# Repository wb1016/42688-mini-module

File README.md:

# 42688-mini-module
small module for ICM-42688-P compatible with BMI160 module form factor. supports I2C, I3C, SPI.

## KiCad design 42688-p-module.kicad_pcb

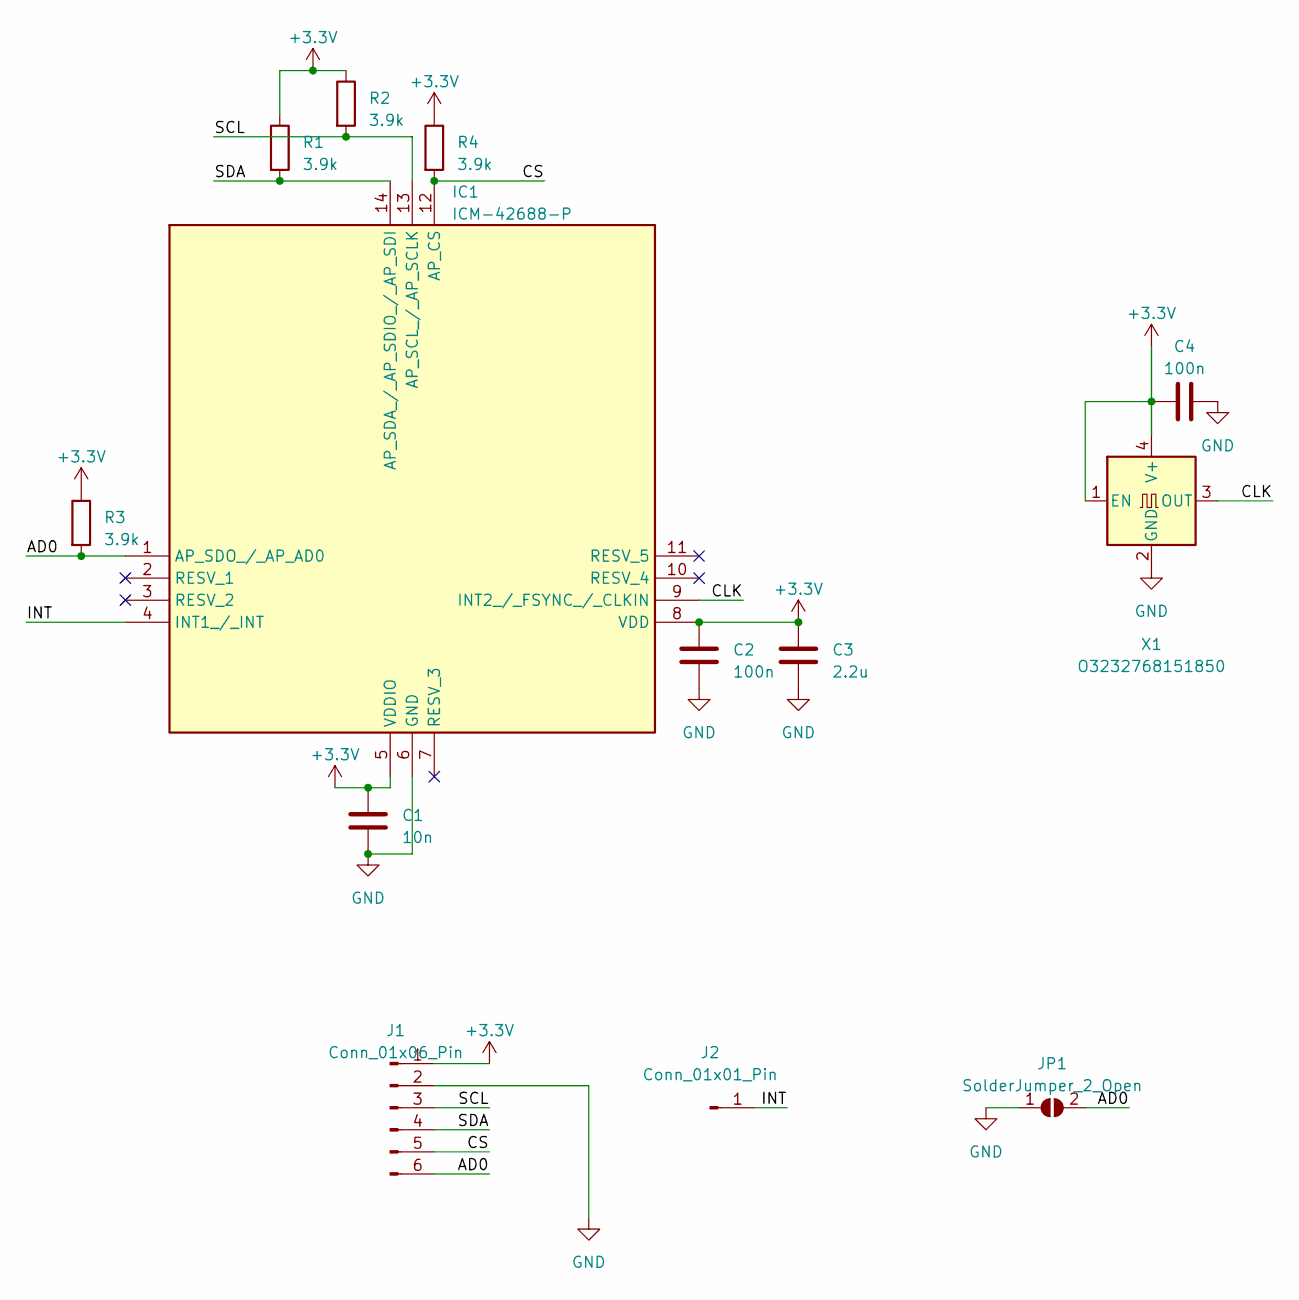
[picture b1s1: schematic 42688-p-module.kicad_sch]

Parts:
C1: 10n; C_0402_1005Metric
C2, C4: 100n; C_0402_1005Metric
C3: 2.2u; C_0603_1608Metric
IC1: ICM-42688-P; IIM42352; Mouser Part Number 410-ICM-42688-P
J1: Conn_01x06_Pin; PinHeader_1x06_P2.54mm_Vertical
J2: Conn_01x01_Pin; PinHeader_1x01_P2.54mm_Vertical
JP1: SolderJumper_2_Open; SolderJumper-2_P1.3mm_Open_TrianglePad1.0x1.5mm
R1, R2, R3, R4: 3.9k; R_0402_1005Metric
X1: O3232768151850; Oscillator_SMD_EuroQuartz_XO32-4Pin_3.2x2.5mm; LCSC Part C390802

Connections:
+3.3V: C1.1, C2.1, C3.1, C4.1, IC1.5 (VDDIO), IC1.8 (VDD), J1.1, R1.1, R2.1, R3.1, R4.1, X1.1 (EN), X1.4 (V+)
/AD0: IC1.1 (AP_SDO_/_AP_AD0), J1.6, JP1.2 (B), R3.2
/CLK: IC1.9 (INT2_/_FSYNC_/_CLKIN), X1.3 (OUT)
/CS: IC1.12 (AP_CS), J1.5, R4.2
/INT: IC1.4 (INT1_/_INT), J2.1
/SCL: IC1.13 (AP_SCL_/_AP_SCLK), J1.3, R2.2
/SDA: IC1.14 (AP_SDA_/_AP_SDIO_/_AP_SDI), J1.4, R1.2
GND: C1.2, C2.2, C3.2, C4.2, IC1.6 (GND), J1.2, JP1.1 (A), X1.2 (GND)

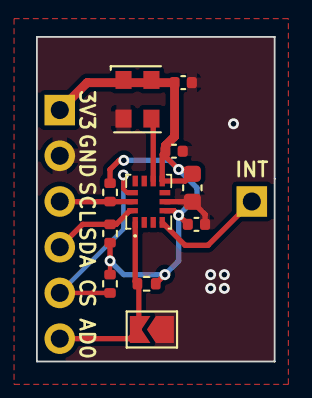
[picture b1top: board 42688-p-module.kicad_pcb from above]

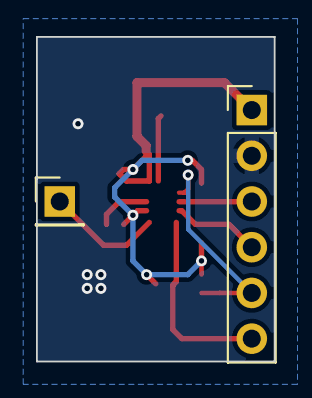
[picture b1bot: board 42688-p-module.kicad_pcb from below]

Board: 2 copper layers, 13.2 x 18.0 mm, 13 parts (2 on the bottom side), 8 nets.

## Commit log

2024-02-26 support SPI
2024-02-26 readme
